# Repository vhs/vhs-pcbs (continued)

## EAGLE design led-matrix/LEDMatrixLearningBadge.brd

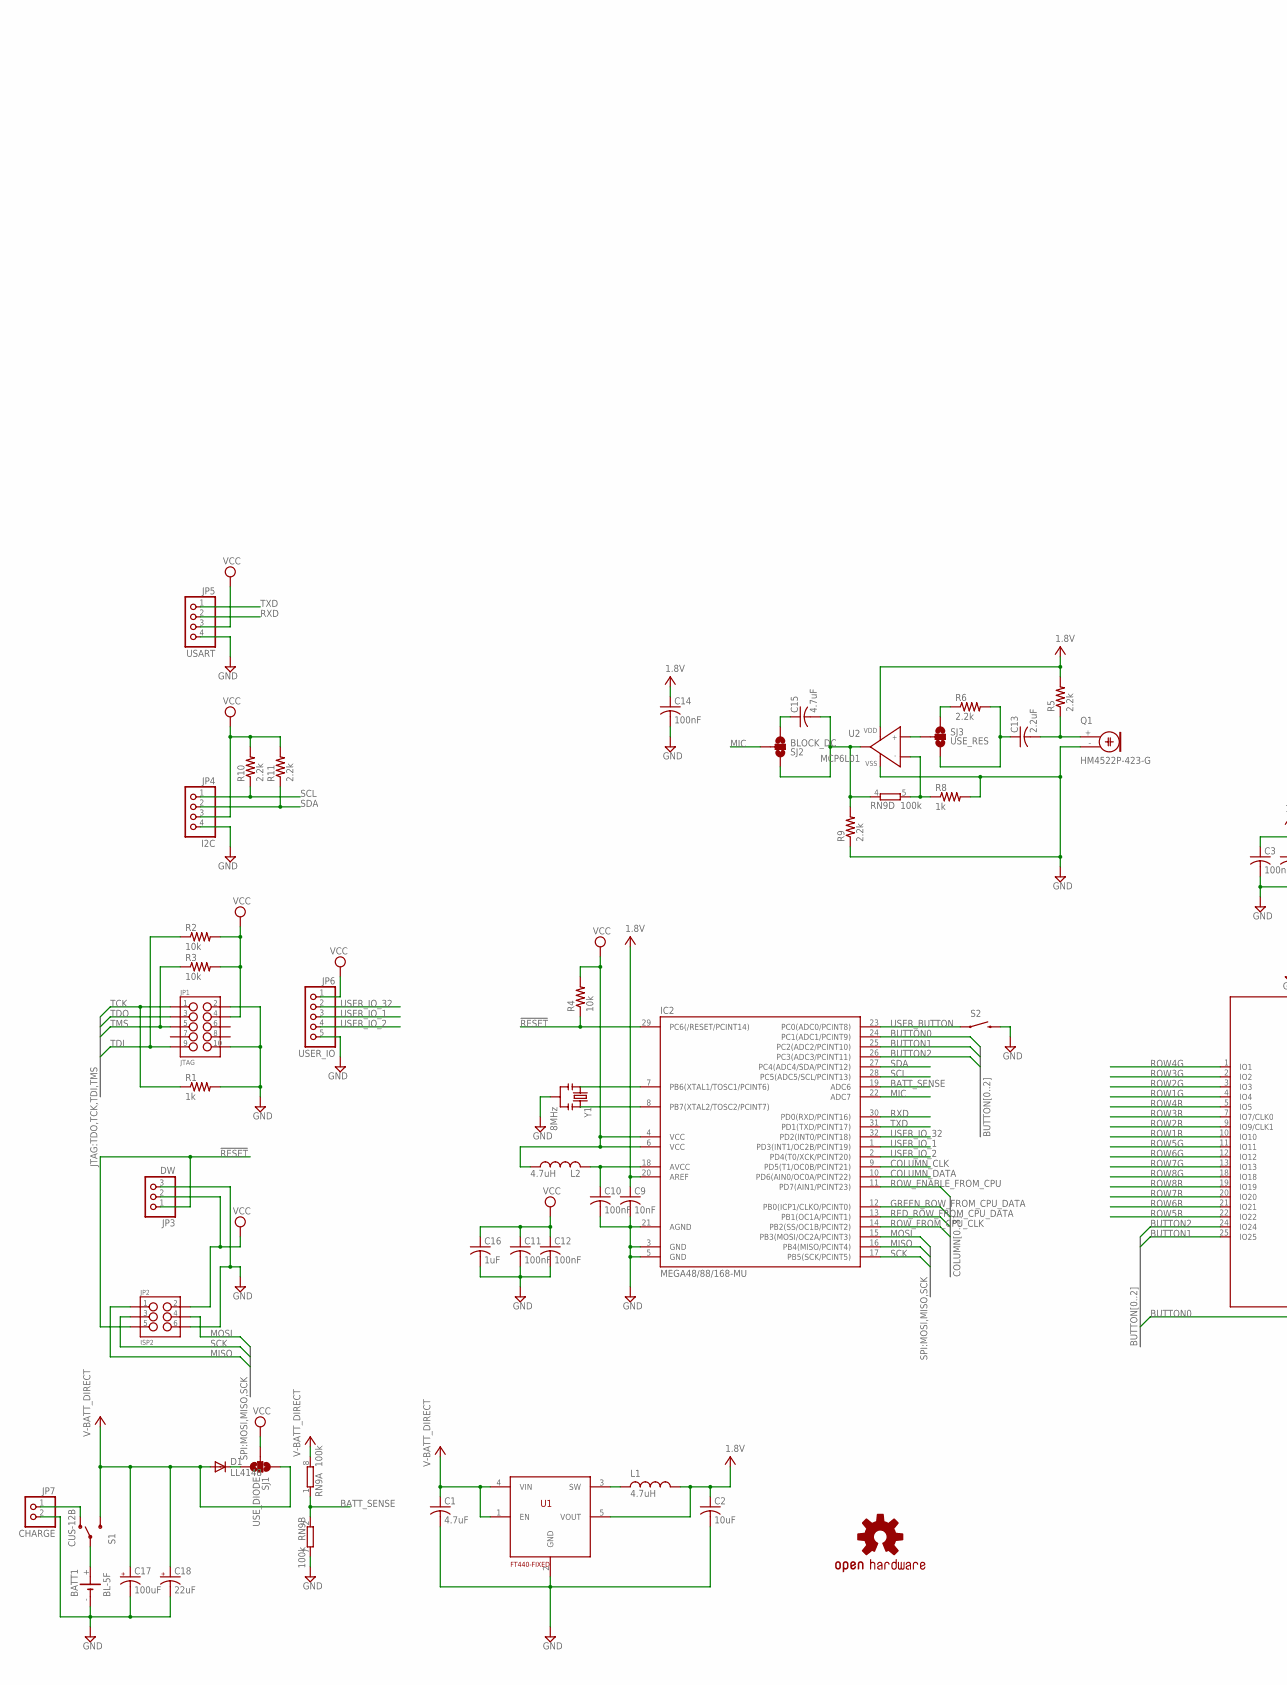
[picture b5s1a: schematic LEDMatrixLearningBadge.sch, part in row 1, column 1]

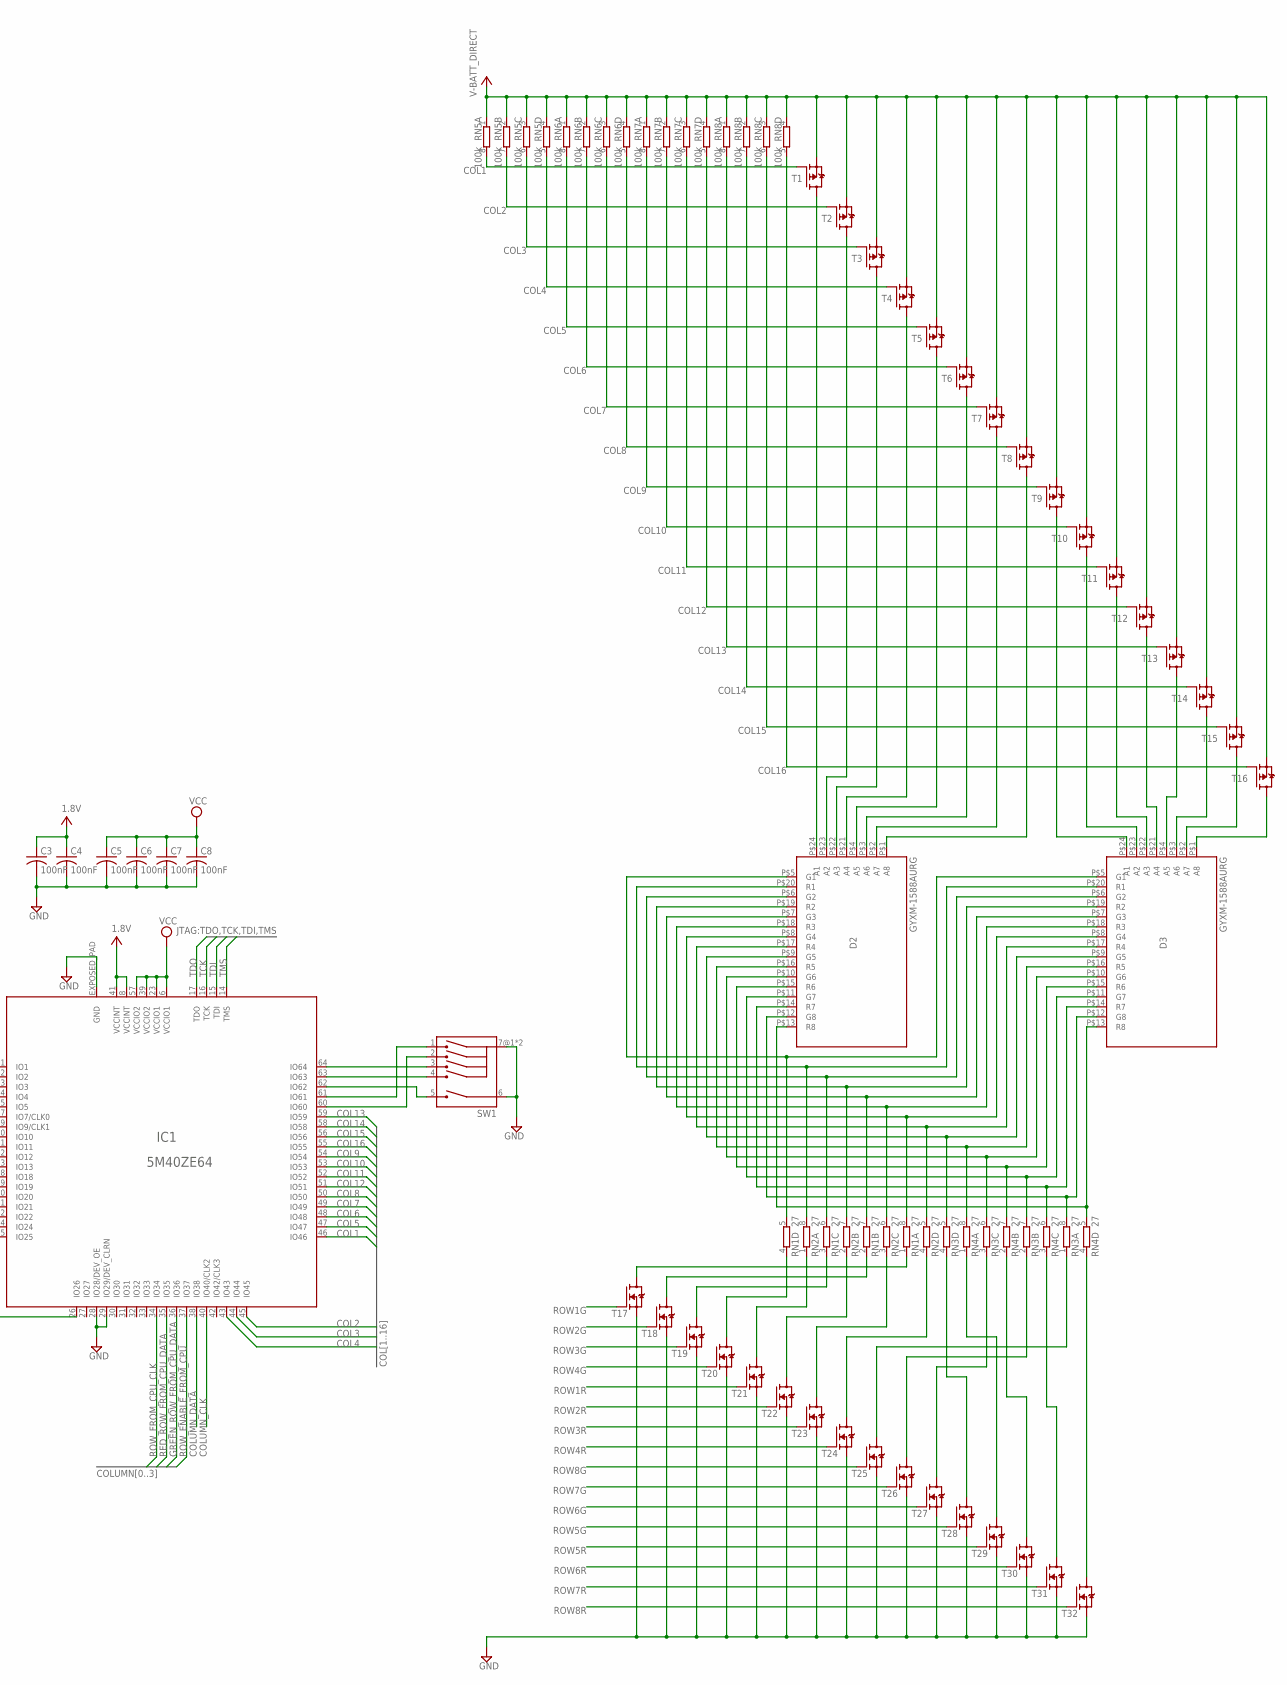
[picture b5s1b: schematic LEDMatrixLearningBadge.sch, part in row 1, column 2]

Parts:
BATT1: BL-5F; NOKIA_BL-5F_INCL_HOLDER
C1, C15: 4.7uF; C0603
C2: 10uF; C0508
C3, C4, C5, C6, C7, C8, C10, C11, C12, C14: 100nF; C0603
C9: 10nF; C0603
C13: 2.2uF; C0603
C16: 1uF; C0603
C17: 100uF; C/6032-28R
C18: 22uF; D/7343-31R
D1: LL4148; SOD80C
D2, D3: GYXM-1588AURG
IC1: 5M40ZE64; EQFP64
IC2: MEGA48/88/168-MU; MLF32
JP1: JTAG; 2X5_POGO
JP2: ISP2; 2X3_POGO
JP3: DW; 1X03
JP4: I2C; 1X04
JP5: USART; 1X04
JP6: USER_IO; 1X05
JP7: CHARGE; 1X02
L1, L2: 4.7uH; 0603
LOGO1: OSHW-LOGOS; OSHW-LOGO-S
Q1: HM4522P-423-G; 4.5ELECTRET
R1, R8: 1k; R0603
R2, R3, R4: 10k; R0603
R5, R6, R9, R10, R11: 2.2k; R0603
RN1, RN2, RN3, RN4: 27; 0603-ARV
RN5, RN6, RN7, RN8, RN9: 100k; 0603-ARV
S1: CUS-12B; SWITCH-SPST-SMD-A
S2: SWITCH-MOMENTARY-212MM; TACTILE-PTH-12MM
SJ1: USE_DIODE; SJ_3_PASTE1&2
SJ2: BLOCK_DC; SJ_3_PASTE1&2
SJ3: USE_RES; SJ_3_PASTE1&2
SW1: 4_DIRECTIONAL_JOYSTICK_PLUS_CENTER; EVQWH
T1, T2, T3, T4, T5, T6, T7, T8, T9, T10, T11, T12, T13, T14, T15, T16: ZXM61P03; SOT23
T17, T18, T19, T20, T21, T22, T23, T24, T25, T26, T27, T28, T29, T30, T31, T32: DMN65D8L; SOT23
U1: FT440-FIXED; SOT23-5
U2: MCP6L01; SOT23-5
Y1: 8MHz; RESONATOR-SMD

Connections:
1.8V: C2.P$1 (1), C3.1, C4.1, C9.1, C14.1, IC1.8 (VCCINT), IC1.41 (VCCINT), IC2.20 (AREF), L1.2, R5.2, U1.5 (VOUT), U2.P5 (VDD)
!RESET: IC2.29 (PC6(/RESET/PCINT14)), JP2.P$5 (5), JP3.1, R4.1
+V-BATT_DIRECT: C1.1, C17.+, C18.+, D1.A, RN5.1, RN5.2 (1), RN5.3 (1), RN5.4 (1), RN6.1, RN6.2 (1), RN6.3 (1), RN6.4 (1), RN7.1, RN7.2 (1), RN7.3 (1), RN7.4 (1), RN8.1, RN8.2 (1), RN8.3 (1), RN8.4 (1), RN9.8 (2), S1.3 (S), SJ1.1, T1.2 (S), T2.2 (S), T3.2 (S), T4.2 (S), T5.2 (S), T6.2 (S), T7.2 (S), T8.2 (S), T9.2 (S), T10.2 (S), T11.2 (S), T12.2 (S), T13.2 (S), T14.2 (S), T15.2 (S), T16.2 (S), U1.1 (EN), U1.4 (VIN)
BATT_SENSE: IC2.19 (ADC6), RN9.1, RN9.2 (1)
BUTTON0: IC1.26 (IO26), IC2.24 (PC1(ADC1/PCINT9))
BUTTON1: IC1.25 (IO25), IC2.25 (PC2(ADC2/PCINT10))
BUTTON2: IC1.24 (IO24), IC2.26 (PC3(ADC3/PCINT11))
COL1: IC1.46 (IO46), RN5.8 (2), T1.1 (G)
COL2: IC1.45 (IO45), RN5.7 (2), T2.1 (G)
COL3: IC1.44 (IO44), RN5.6 (2), T3.1 (G)
COL4: IC1.43 (IO43), RN5.5 (2), T4.1 (G)
COL5: IC1.47 (IO47), RN6.8 (2), T5.1 (G)
COL6: IC1.48 (IO48), RN6.7 (2), T6.1 (G)
COL7: IC1.49 (IO49), RN6.6 (2), T7.1 (G)
COL8: IC1.50 (IO50), RN6.5 (2), T8.1 (G)
COL9: IC1.54 (IO54), RN7.8 (2), T9.1 (G)
COL10: IC1.53 (IO53), RN7.7 (2), T10.1 (G)
COL11: IC1.52 (IO52), RN7.6 (2), T11.1 (G)
COL12: IC1.51 (IO51), RN7.5 (2), T12.1 (G)
COL13: IC1.59 (IO59), RN8.8 (2), T13.1 (G)
COL14: IC1.58 (IO58), RN8.7 (2), T14.1 (G)
COL15: IC1.56 (IO56), RN8.6 (2), T15.1 (G)
COL16: IC1.55 (IO55), RN8.5 (2), T16.1 (G)
COLUMN_CLK: IC1.40 (IO40/CLK2), IC2.9 (PD5(T1/OC0B/PCINT21))
COLUMN_DATA: IC1.38 (IO38), IC2.10 (PD6(AIN0/OC0A/PCINT22))
GND: BATT1.-, C1.2, C2.P$2 (2), C3.2, C4.2, C5.2, C6.2, C7.2, C8.2, C9.2, C10.2, C11.2, C12.2, C14.2, C16.2, C17.-, C18.-, IC1.28 (IO28/DEV_OE), IC1.29 (IO29/DEV_CLRN), IC1.EXPOSED_PAD (GND), IC2.3 (GND), IC2.5 (GND), IC2.21 (AGND), JP1.P$2 (2), JP1.P$10 (10), JP2.P$6 (6), JP3.3, JP4.4, JP5.4, JP6.5, JP7.2, Q1.- (1), R1.2, R8.2, R9.1, RN9.7 (2), S2.3 (2), SW1.6, SW1.7@1, SW1.7@2, T17.2 (S), T18.2 (S), T19.2 (S), T20.2 (S), T21.2 (S), T22.2 (S), T23.2 (S), T24.2 (S), T25.2 (S), T26.2 (S), T27.2 (S), T28.2 (S), T29.2 (S), T30.2 (S), T31.2 (S), T32.2 (S), U1.2 (GND), U2.P2 (VSS), Y1.2
GREEN_ROW_FROM_CPU_DATA: IC1.36 (IO36), IC2.12 (PB0(ICP1/CLKO/PCINT0))
MIC: IC2.22 (ADC7), SJ2.2
MISO: IC2.16 (PB4(MISO/PCINT4)), JP2.P$1 (1)
MOSI: IC2.15 (PB3(MOSI/OC2A/PCINT3)), JP2.P$4 (4)
unnamed: SJ3.2, U2.P3 (IN+)
unnamed: C13.2, Q1.+ (2), R5.1
unnamed: R6.1, SJ3.1
unnamed: R8.1, RN9.5 (2), U2.P4 (IN-)
unnamed: C15.1, SJ2.3
unnamed: C15.2, R9.2, RN9.4 (1), SJ2.1, U2.P1 (OUT)
unnamed: C13.1, R6.2, SJ3.3
unnamed: D2.P$1 (A8), T8.3 (D)
unnamed: D1.C, SJ1.3
unnamed: L1.1, U1.3 (SW)
unnamed: C10.1, IC2.18 (AVCC), L2.2
unnamed: D2.P$2 (A7), T7.3 (D)
unnamed: D2.P$3 (A6), T6.3 (D)
unnamed: D2.P$4 (A5), T5.3 (D)
unnamed: D2.P$21 (A4), T4.3 (D)
unnamed: D2.P$22 (A3), T3.3 (D)
unnamed: D2.P$23 (A2), T2.3 (D)
unnamed: D2.P$24 (A1), T1.3 (D)
unnamed: D3.P$24 (A1), T9.3 (D)
unnamed: D3.P$1 (A8), T16.3 (D)
unnamed: D3.P$2 (A7), T15.3 (D)
unnamed: D3.P$3 (A6), T14.3 (D)
unnamed: D3.P$4 (A5), T13.3 (D)
unnamed: D3.P$21 (A4), T12.3 (D)
unnamed: D3.P$22 (A3), T11.3 (D)
unnamed: D3.P$23 (A2), T10.3 (D)
unnamed: D2.P$13 (R8), D3.P$13 (R8), RN4.5 (2)
unnamed: D2.P$12 (G8), D3.P$12 (G8), RN3.8 (2)
unnamed: D2.P$14 (R7), D3.P$14 (R7), RN4.6 (2)
unnamed: D2.P$11 (G7), D3.P$11 (G7), RN3.7 (2)
unnamed: D2.P$15 (R6), D3.P$15 (R6), RN4.7 (2)
unnamed: D2.P$10 (G6), D3.P$10 (G6), RN3.6 (2)
unnamed: D2.P$16 (R5), D3.P$16 (R5), RN4.8 (2)
unnamed: D2.P$9 (G5), D3.P$9 (G5), RN3.5 (2)
unnamed: D2.P$17 (R4), D3.P$17 (R4), RN2.5 (2)
unnamed: D2.P$8 (G4), D3.P$8 (G4), RN1.8 (2)
unnamed: D2.P$18 (R3), D3.P$18 (R3), RN2.6 (2)
unnamed: D2.P$7 (G3), D3.P$7 (G3), RN1.7 (2)
unnamed: D2.P$19 (R2), D3.P$19 (R2), RN2.7 (2)
unnamed: D2.P$6 (G2), D3.P$6 (G2), RN1.6 (2)
unnamed: D2.P$20 (R1), D3.P$20 (R1), RN2.8 (2)
unnamed: D2.P$5 (G1), D3.P$5 (G1), RN1.5 (2)
unnamed: BATT1.+, S1.2
unnamed: IC1.64 (IO64), SW1.3
unnamed: IC1.63 (IO63), SW1.4
unnamed: IC1.62 (IO62), SW1.5
unnamed: IC1.60 (IO60), SW1.2
unnamed: IC1.61 (IO61), SW1.1
unnamed: RN4.4 (1), T32.3 (D)
unnamed: IC2.7 (PB6(XTAL1/TOSC1/PCINT6)), Y1.1
unnamed: IC2.8 (PB7(XTAL2/TOSC2/PCINT7)), Y1.3
unnamed: JP7.1, S1.1 (O)
unnamed: RN4.3 (1), T31.3 (D)
unnamed: RN4.2 (1), T30.3 (D)
unnamed: RN4.1, T29.3 (D)
unnamed: RN3.4 (1), T28.3 (D)
unnamed: RN3.3 (1), T27.3 (D)
unnamed: RN3.2 (1), T26.3 (D)
unnamed: RN3.1, T25.3 (D)
unnamed: RN2.4 (1), T24.3 (D)
unnamed: RN2.3 (1), T23.3 (D)
unnamed: RN2.2 (1), T22.3 (D)
unnamed: RN2.1, T21.3 (D)
unnamed: RN1.4 (1), T20.3 (D)
unnamed: RN1.3 (1), T19.3 (D)
unnamed: RN1.2 (1), T18.3 (D)
unnamed: RN1.1, T17.3 (D)
RED_ROW_FROM_CPU_DATA: IC1.35 (IO35), IC2.13 (PB1(OC1A/PCINT1))
ROW1G: IC1.4 (IO4), T17.1 (G)
ROW1R: IC1.10 (IO10), T21.1 (G)
ROW2G: IC1.3 (IO3), T18.1 (G)
ROW2R: IC1.9 (IO9/CLK1), T22.1 (G)
ROW3G: IC1.2 (IO2), T19.1 (G)
ROW3R: IC1.7 (IO7/CLK0), T23.1 (G)
ROW4G: IC1.1 (IO1), T20.1 (G)
ROW4R: IC1.5 (IO5), T24.1 (G)
ROW5G: IC1.11 (IO11), T28.1 (G)
ROW5R: IC1.22 (IO22), T29.1 (G)
ROW6G: IC1.12 (IO12), T27.1 (G)
ROW6R: IC1.21 (IO21), T30.1 (G)
ROW7G: IC1.13 (IO13), T26.1 (G)
ROW7R: IC1.20 (IO20), T31.1 (G)
ROW8G: IC1.18 (IO18), T25.1 (G)
ROW8R: IC1.19 (IO19), T32.1 (G)
ROW_ENABLE_FROM_CPU: IC1.37 (IO37), IC2.11 (PD7(AIN1/PCINT23))
ROW_FROM_CPU_CLK: IC1.34 (IO34), IC2.14 (PB2(SS/OC1B/PCINT2))
RXD: IC2.30 (PD0(RXD/PCINT16)), JP5.2
SCK: IC2.17 (PB5(SCK/PCINT5)), JP2.P$3 (3)
SCL: IC2.28 (PC5(ADC5/SCL/PCINT13)), JP4.1, R10.1
SDA: IC2.27 (PC4(ADC4/SDA/PCINT12)), JP4.2, R11.1
TCK: IC1.16 (TCK), JP1.P$1 (1), R1.1
TDI: IC1.15 (TDI), JP1.P$9 (9), R2.1
TDO: IC1.17 (TDO), JP1.P$3 (3)
TMS: IC1.14 (TMS), JP1.P$5 (5), R3.1
TXD: IC2.31 (PD1(TXD/PCINT17)), JP5.1
USER_BUTTON: IC2.23 (PC0(ADC0/PCINT8)), S2.1
USER_IO_1: IC2.1 (PD3(INT1/OC2B/PCINT19)), JP6.3
USER_IO_2: IC2.2 (PD4(T0/XCK/PCINT20)), JP6.4
USER_IO_32: IC2.32 (PD2(INT0/PCINT18)), JP6.2
VCC: C5.1, C6.1, C7.1, C8.1, C11.1, C12.1, C16.1, IC1.6 (VCCIO1), IC1.23 (VCCIO1), IC1.39 (VCCIO2), IC1.57 (VCCIO2), IC2.4 (VCC), IC2.6 (VCC), JP1.P$4 (4), JP2.P$2 (2), JP3.2, JP4.3, JP5.3, JP6.1, L2.1, R2.2, R3.2, R4.2, R10.2, R11.2, SJ1.2

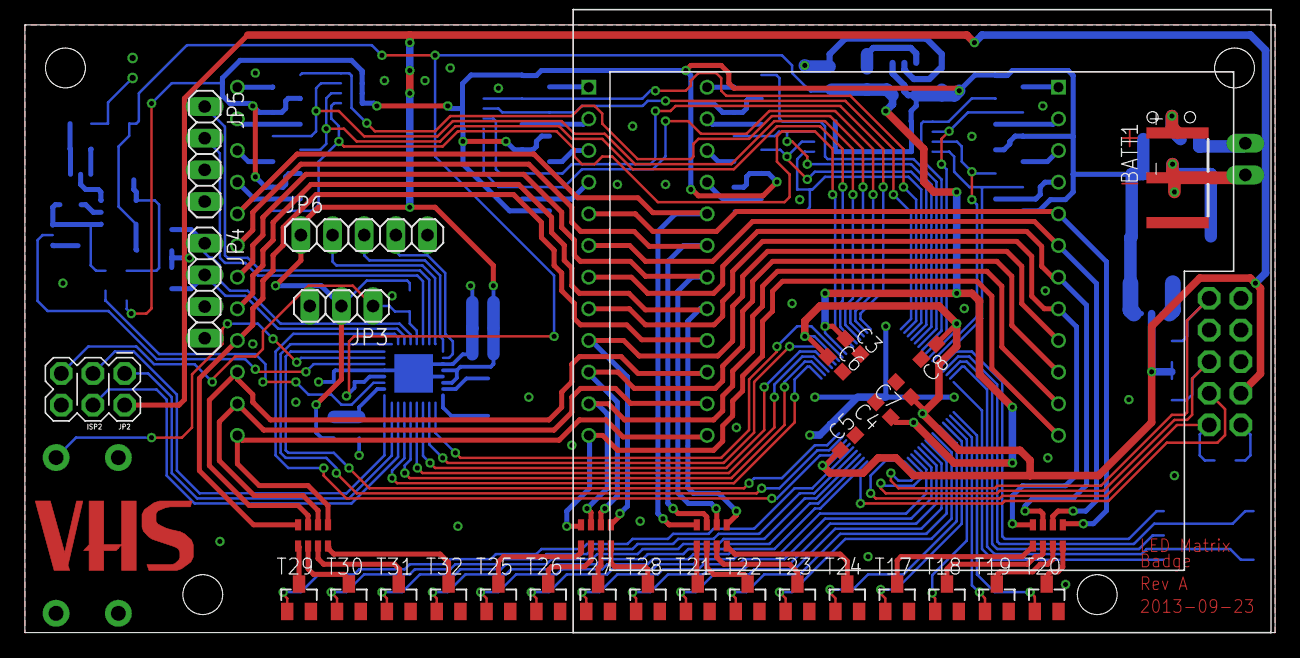
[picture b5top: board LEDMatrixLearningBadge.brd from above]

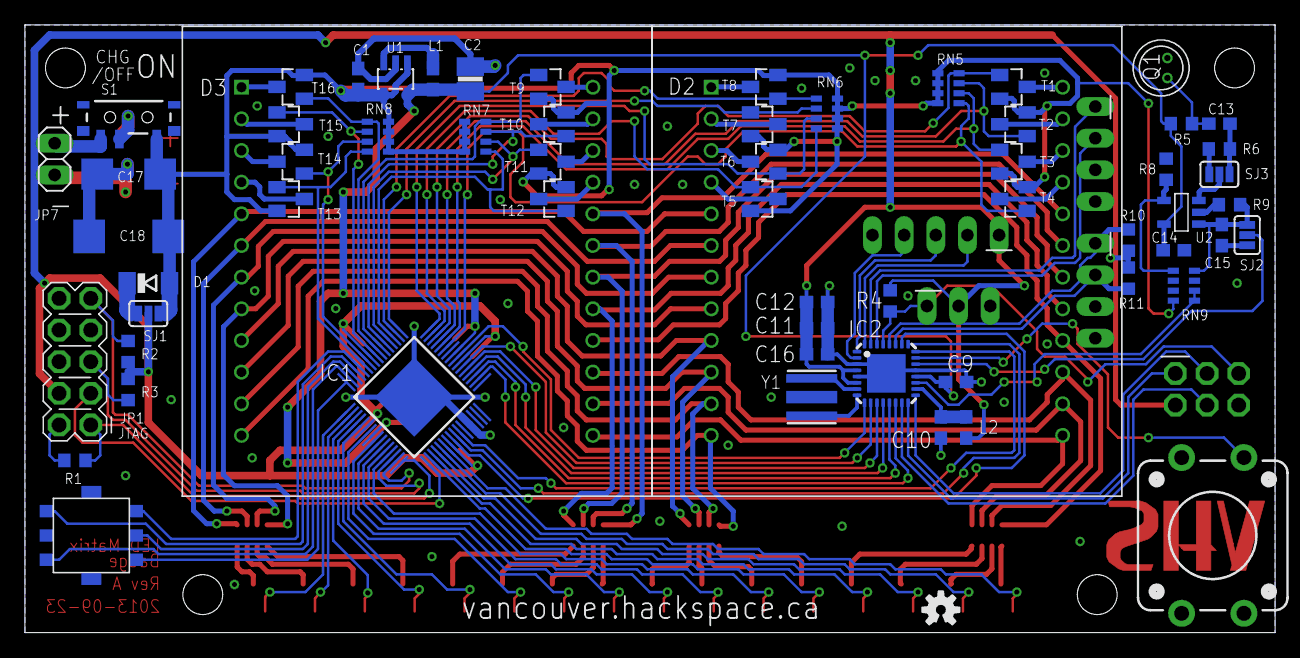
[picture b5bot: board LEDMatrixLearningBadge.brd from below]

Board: 2 copper layers, 100.3 x 48.8 mm, 96 parts (63 on the bottom side), 130 nets.

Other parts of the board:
U$5: VHS-SML

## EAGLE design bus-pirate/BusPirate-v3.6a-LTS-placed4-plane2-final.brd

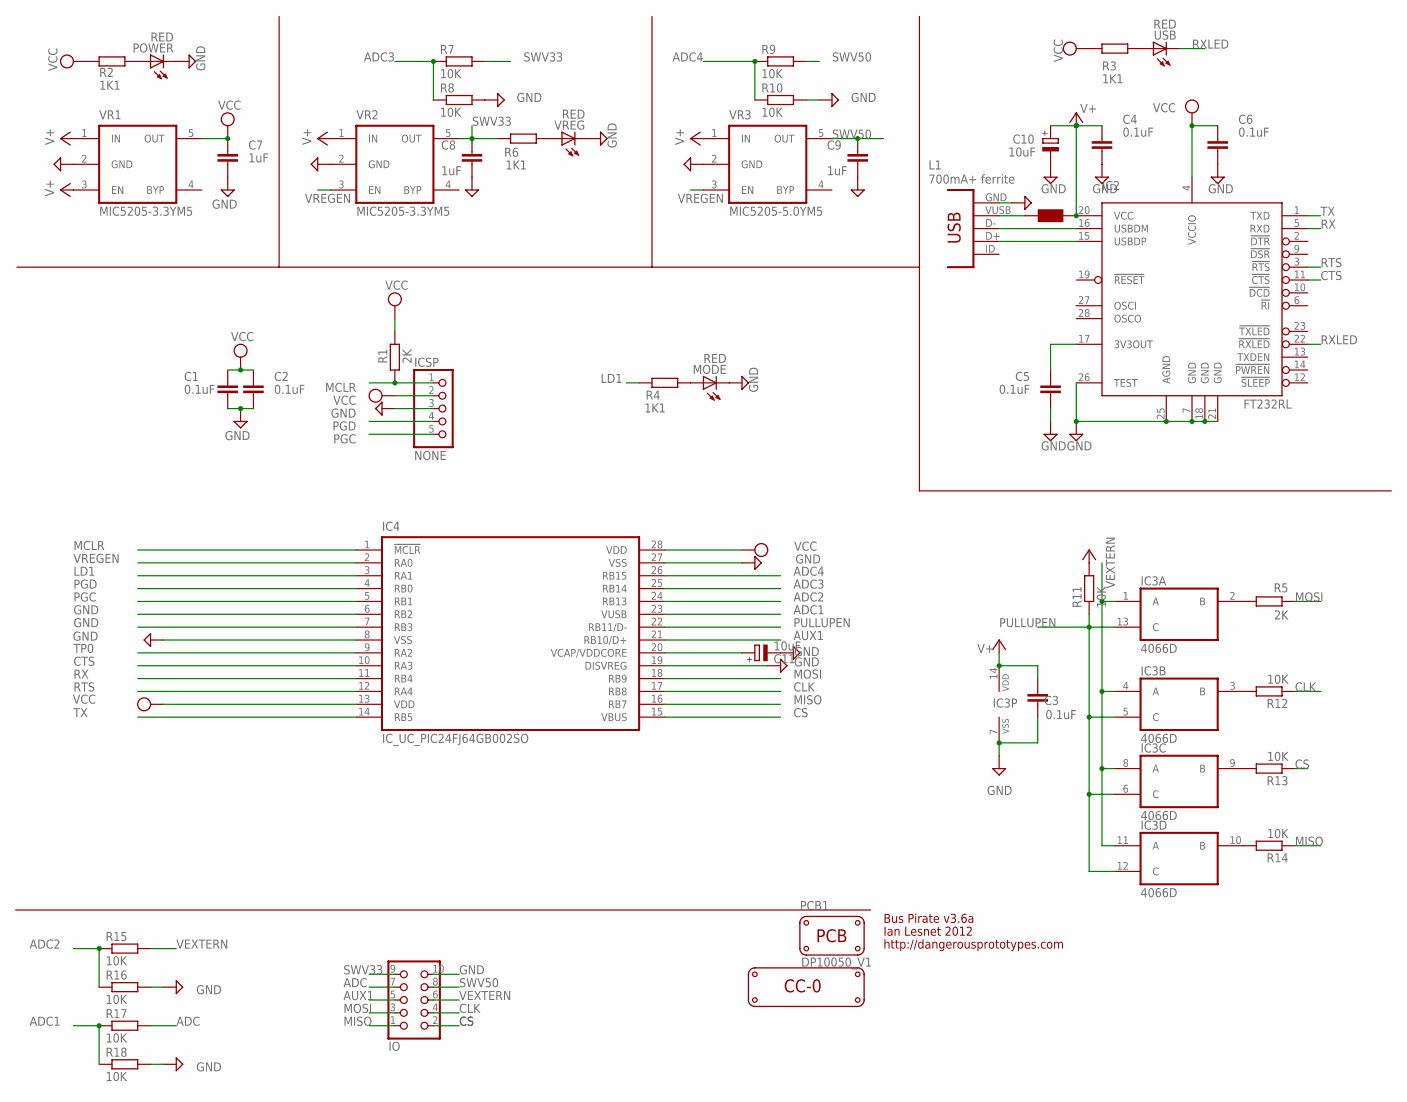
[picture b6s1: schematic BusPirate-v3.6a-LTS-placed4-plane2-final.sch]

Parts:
C1, C2, C3, C4, C5, C6: 0.1uF; C1206
C7, C8, C9: 1uF; C1206
C10, C11: 10uF; CT3528
IC2: FT232RL; SSOP28
IC3: 4066D; SO14
IC4: IC_UC_PIC24FJ64GB002SO; SOIC-28W
ICSP: NONE; 1X05
IO: CON_HEADER_2X05-PTH+SHROUDED_B; PINSHRD_PTH_2X05B
J1: CON-USB-MINI-BUSB1; CONN_USB_MINI-B
L1: 700mA+ ferrite; WE-KI_0805_B
LOGO1: LOGO_CC-0
MODE: RED; CHIPLED_1206
PCB1: PCB_DP_RECTANGLE-50X100; DP10050_V1
POWER: RED; CHIPLED_1206
R1, R5: 2K; R1206
R2, R3, R4, R6: 1K1; R1206
R7, R8, R9, R10, R11, R12, R13, R14, R15, R16, R17, R18: 10K; R1206
USB: RED; CHIPLED_1206
VR1, VR2: MIC5205-3.3YM5; SOT-23-5
VR3: MIC5205-5.0YM5; SOT-23-5
VREG: RED; CHIPLED_1206

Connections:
$N26: J1.VUSB, L1.2 (1)
ADC: IO.7, R17.2
ADC1: IC4.23 (VUSB), R17.1, R18.1
ADC2: IC4.24 (RB13), R15.1, R16.1
ADC3: IC4.25 (RB14), R7.1, R8.1
ADC4: IC4.26 (RB15), R9.1, R10.1
AUX1: IC4.21 (RB10/D+), IO.5
CLK: IC4.17 (RB8), IO.4, R12.1
CS: IC4.15 (VBUS), IO.2, R13.1
CTS: IC2.11 (!CTS), IC4.10 (RA3)
GND: C1.2, C2.2, C3.2, C4.2, C5.2, C6.2, C7.2, C8.2, C9.2, C10.-, C11.-, IC2.7 (GND), IC2.18 (GND), IC2.21 (GND), IC2.25 (AGND), IC2.26 (TEST), IC3.7 (VSS), IC4.6 (RB2), IC4.7 (RB3), IC4.8 (VSS), IC4.19 (DISVREG), IC4.27 (VSS), ICSP.3, IO.10, J1.GND, MODE.C, POWER.C, R8.2, R10.2, R16.2, R18.2, VR1.2 (GND), VR2.2 (GND), VR3.2 (GND), VREG.C
LD1: IC4.3 (RA1), R4.2
MCLR: IC4.1 (!MCLR), ICSP.1, R1.1
MISO: IC4.16 (RB7), IO.1, R14.1
MOSI: IC4.18 (RB9), IO.3, R5.1
unnamed: IC3.2 (B), R5.2
unnamed: IC3.3 (B), R12.2
unnamed: C11.+, IC4.20 (VCAP/VDDCORE)
unnamed: IC3.9 (B), R13.2
unnamed: IC3.10 (B), R14.2
unnamed: MODE.A, R4.1
unnamed: POWER.A, R2.1
unnamed: C5.1, IC2.17 (3V3OUT)
unnamed: R3.1, USB.A
unnamed: IC2.15 (USBDP), J1.D+
unnamed: IC2.16 (USBDM), J1.D-
unnamed: R6.1, VREG.A
PGC: IC4.5 (RB1), ICSP.5
PGD: IC4.4 (RB0), ICSP.4
PULLUPEN: IC3.5 (C), IC3.6 (C), IC3.12 (C), IC3.13 (C), IC4.22 (RB11/D-), R11.1
RTS: IC2.3 (!RTS), IC4.12 (RA4)
RX: IC2.5 (RXD), IC4.11 (RB4)
RXLED: IC2.22 (!RXLED), USB.C
SWV33: C8.1, IO.9, R6.2, R7.2, VR2.5 (OUT)
SWV50: C9.1, IO.8, R9.2, VR3.5 (OUT)
TP0: IC4.9 (RA2)
TX: IC2.1 (TXD), IC4.14 (RB5)
V+: C3.1, C4.1, C10.+, IC2.20 (VCC), IC3.14 (VDD), L1.1 (2), R11.2, VR1.1 (IN), VR1.3 (EN), VR2.1 (IN), VR3.1 (IN)
VCC: C1.1, C2.1, C6.1, C7.1, IC2.4 (VCCIO), IC4.13 (VDD), IC4.28 (VDD), ICSP.2, R1.2, R2.2, R3.2, VR1.5 (OUT)
VEXTERN: IC3.1 (A), IC3.4 (A), IC3.8 (A), IC3.11 (A), IO.6, R15.2
VREGEN: IC4.2 (RA0), VR2.3 (EN), VR3.3 (EN)

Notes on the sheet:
Bus Pirate v3.6a
Ian Lesnet 2012
http://dangerousprototypes.com

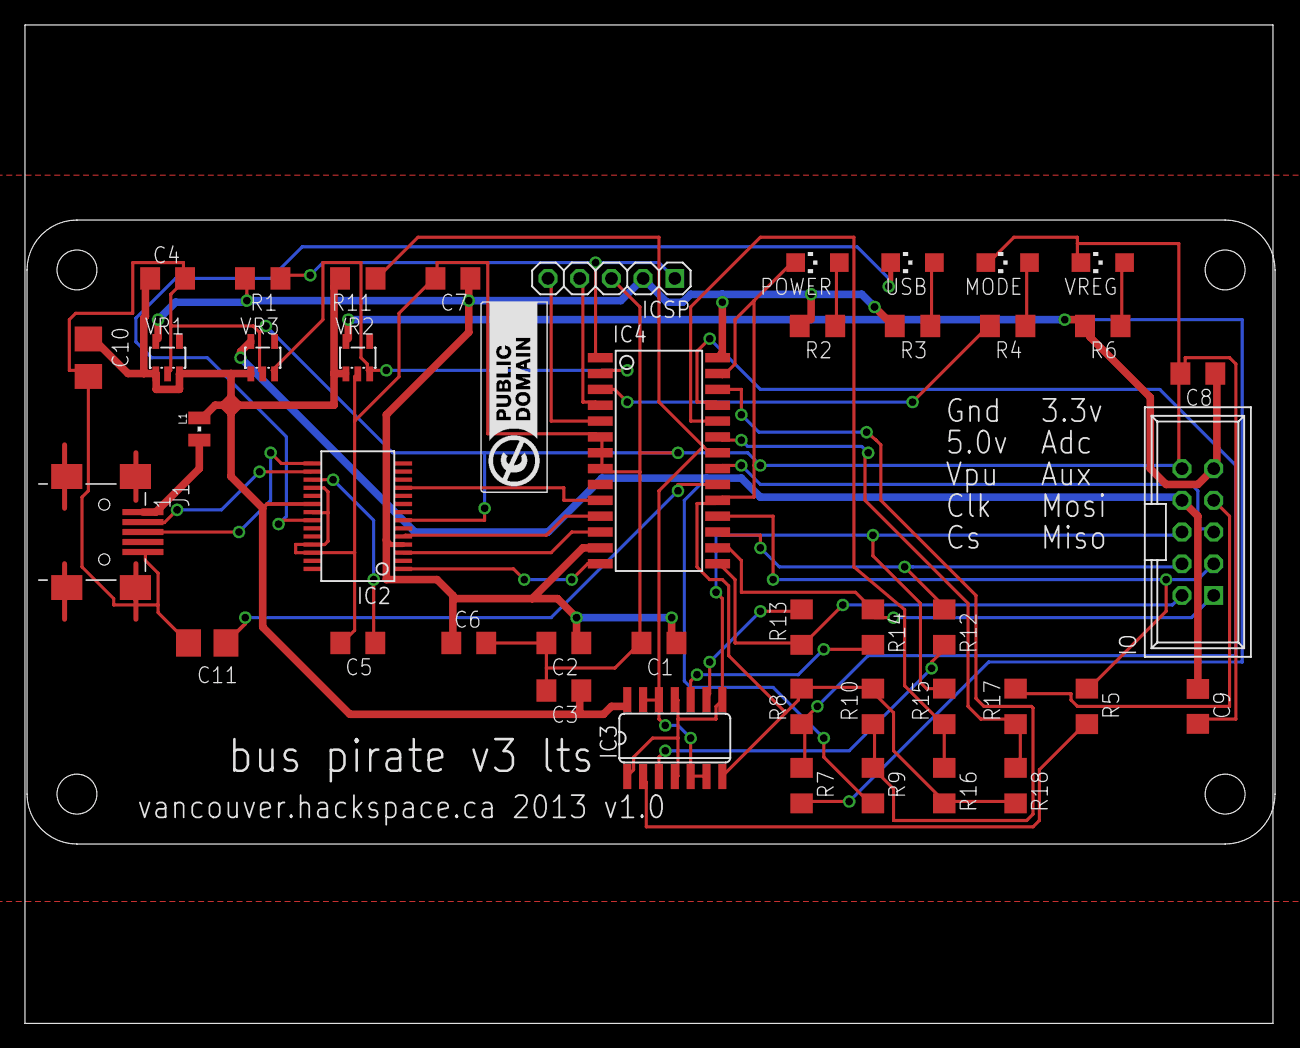
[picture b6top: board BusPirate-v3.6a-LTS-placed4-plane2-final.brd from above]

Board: 2 copper layers, 100.2 x 80.0 mm, 46 parts (1 on the bottom side), 40 nets.

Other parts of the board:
U$1: VHS

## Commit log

2013-08-16 Eagle files as sent to itead studio
2013-08-16 Files from JohnC
    I've attached the schematic and board files. The parts are from the
    Sparkfun Electronics Eagle libraries here:
    https://github.com/sparkfun/SparkFun-Eagle-Libraries
2013-09-30 Rev A of LED Matrix boards for 5th Anniversary SHHH
2013-09-30 Added BOM and PDF version of schematic
2013-09-30 Added license information
2013-10-29 Signal rename
    Renamed CPLD signals to cpu to reflect reworked hdl code
2013-11-11 Added PNG of bus pirate schematic
2013-11-24 Add bpv3 workshop notes
2013-11-29 Added DXF for acrylic base plate
2014-02-12 Add ethernet gateway from http://kehribar.me/hardware/ethernetGateway/
    Reset/Optiboot still not working. Serial proven, ethernet proven.
2014-02-12 Updated instructions for working ethernet gateway with photos
2014-02-12 Update ethernet gateway reset circuit
2014-02-27 Add rev 0.3 schematic png
2014-03-06 Add first draft of workshop notes
2014-03-14 Updated internet of things photos and notes
2014-03-20 Added usb isolator pcb design
2014-03-20 Updated underside photo to show missing component labels
2014-03-20 Updated internet of things notes
2014-03-27 Added source location to readme
2014-03-27 Fix led orientation in photo
2014-03-27 Add small pcb image
2014-03-27 Cropped small image
2014-03-29 Corrected errors in reset wiring
2014-04-01 Added BOM for usb isolator
2014-04-07 Added markdown parts list and photo
2014-04-07 Tidied parts list, added detail
2014-04-07 removed nreable html parts list
2014-04-15 Ad USB isolator workshop materials
2014-07-26 Add MaKey MaKey materials
2014-07-26 Add MaKeyMaKey readme
2014-07-26 Update MakeyMakey README
2014-09-16 Add RFID door controller code
2014-09-16 Add RFID door opener code
2014-09-23 Added non-blocking serial receive, longer auth string
2015-02-18 Add fet shield pdf
2015-03-04 Updated with 0.2" caps and power switch
2015-03-06 Add GTP for usb-isolator
2015-03-08 Change caps to 0.2 pitch, fix silk issues, panelise into 4 per 10x10 panel
2015-03-17 Maker Faire LED board v2.0 as submitted for proto run
2015-04-26 2015 MF PCB final
2015-04-26 Updaed schematic image
2015-06-29 Add final gerbers
2015-06-29 Added Digikey connector part number from Mike
2015-06-30 Added credit to Mike.
2015-07-30 Adding files from day 1 KiCad workshop
2016-03-21 Added files via upload
    docx file of blinky badge soldering instructions updated for the VHS soldering booth at Maker Faire 2015
2016-03-23 Improve Transistor orientation markings
2016-03-31 Improved transistor marking on overlay
2016-03-31 Added VHS blinky badge photos
    Completed 2015 VHS blinky badges. Designed by Tom K. Used at Maker Faire 2015.
2016-03-31 As sent to seeed studio 2016 Maker Faire
2016-03-31 Reorganised badge files
2016-03-31 Removed obsolete panelised files
2016-10-18 Added missing images
2017-02-01 Updated for 2017 with new domain
2017-02-01 Resolved merge conflict by keeping circle.brd
2017-02-01 Removed duplicate gerbers
2017-02-01 Fixed for 2017 with new domain
2017-02-01 Removed extra file
2017-04-19 Added original arduino leonardo eagle files
2017-04-19 Removed PCB file
2017-04-27 Add copies of sparkfun and adafruit libraries Add FET and PWM output to schematic
2017-04-30 Added DirtyPCBs cam/dru files Added DangerousPrototypes libraries
2017-04-30 Add missing DP files
2017-09-15 Create smd-star-build
2017-09-17 Create smd-star-workshop-docs
2017-09-17 Create derp
2017-09-17 workshop slidedeck, links, and instructions
2018-07-18 led-segment display : updated to rev 1.1 to improve alignment of diagonals and enlarge pads to make hand soldering easier. TODO need an indicator to show top of board to reduce confusion. TODO need t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
